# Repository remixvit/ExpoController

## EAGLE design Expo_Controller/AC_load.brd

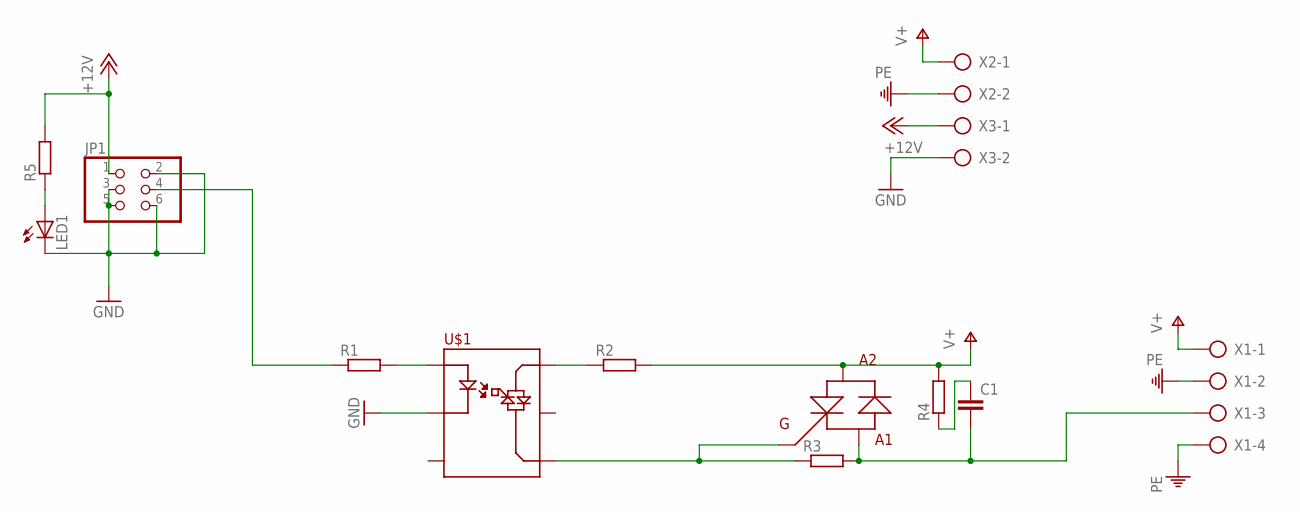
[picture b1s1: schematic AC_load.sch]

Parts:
C1: C-EU102-064X133; C102-064X133
JP1: PINHD-2X3; 2X03
LED1: LEDSML1206; SML1206
R1, R2, R3, R4, R5: R-EU_M1206; M1206
U$1: MOC3043; DIL06
U$2: BTB16; TO220NORM
X1: AK500/4
X2, X3: AK500/2

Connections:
+12V: JP1.1, R5.2, X3.1
GND: JP1.2, JP1.3, JP1.5, JP1.6, LED1.C, U$1.2 (LED_OUT), X3.2
unnamed: R1.2, U$1.1 (LED_IN)
unnamed: C1.2, R3.2, U$2.MT1 (A1), X1.3
unnamed: JP1.4, R1.1
unnamed: R3.1, U$1.4 (SIM2), U$2.GATE (G)
unnamed: R2.1, U$1.6 (SIM1)
unnamed: C1.1, R4.1
unnamed: LED1.A, R5.1
PE: X1.2, X1.4, X2.2
V+: R2.2, R4.2, U$2.MT2 (A2), X1.1, X2.1

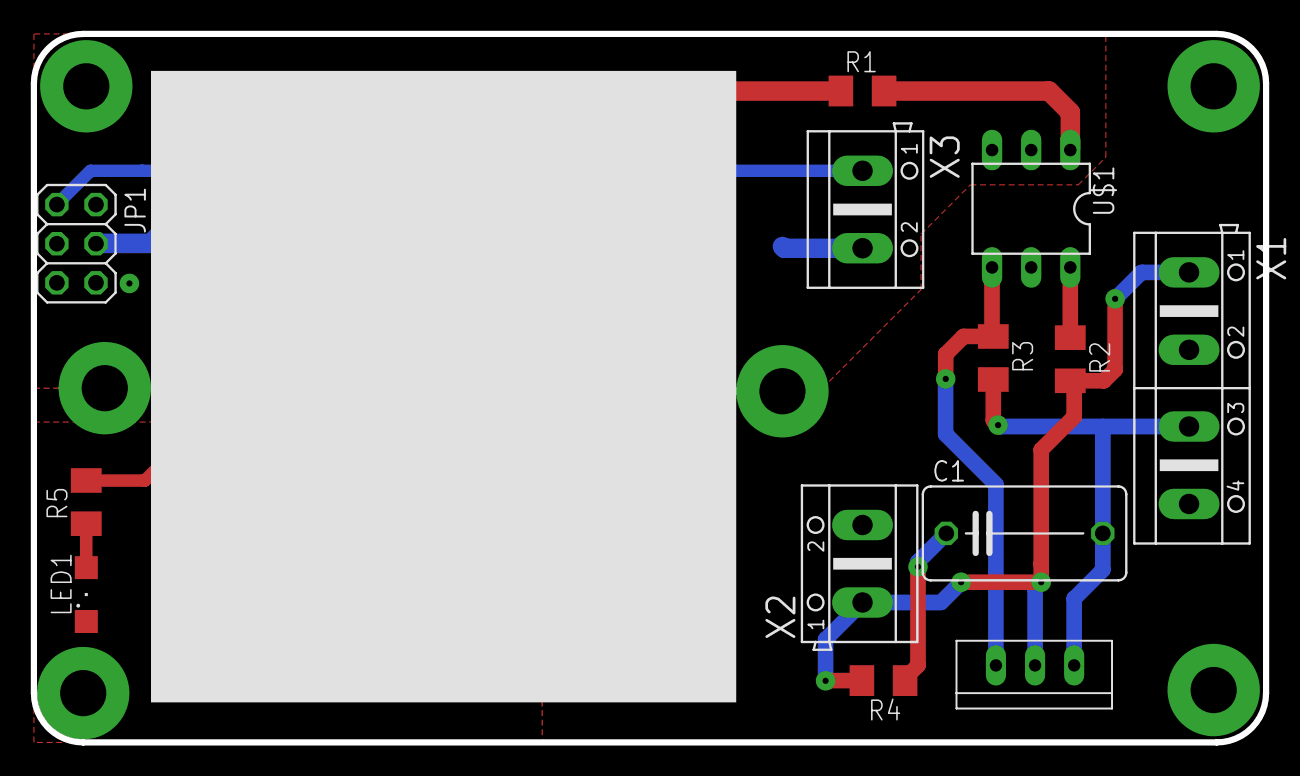
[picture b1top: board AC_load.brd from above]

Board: 2 copper layers, 80.0 x 46.0 mm, 13 parts (0 on the bottom side), 11 nets.

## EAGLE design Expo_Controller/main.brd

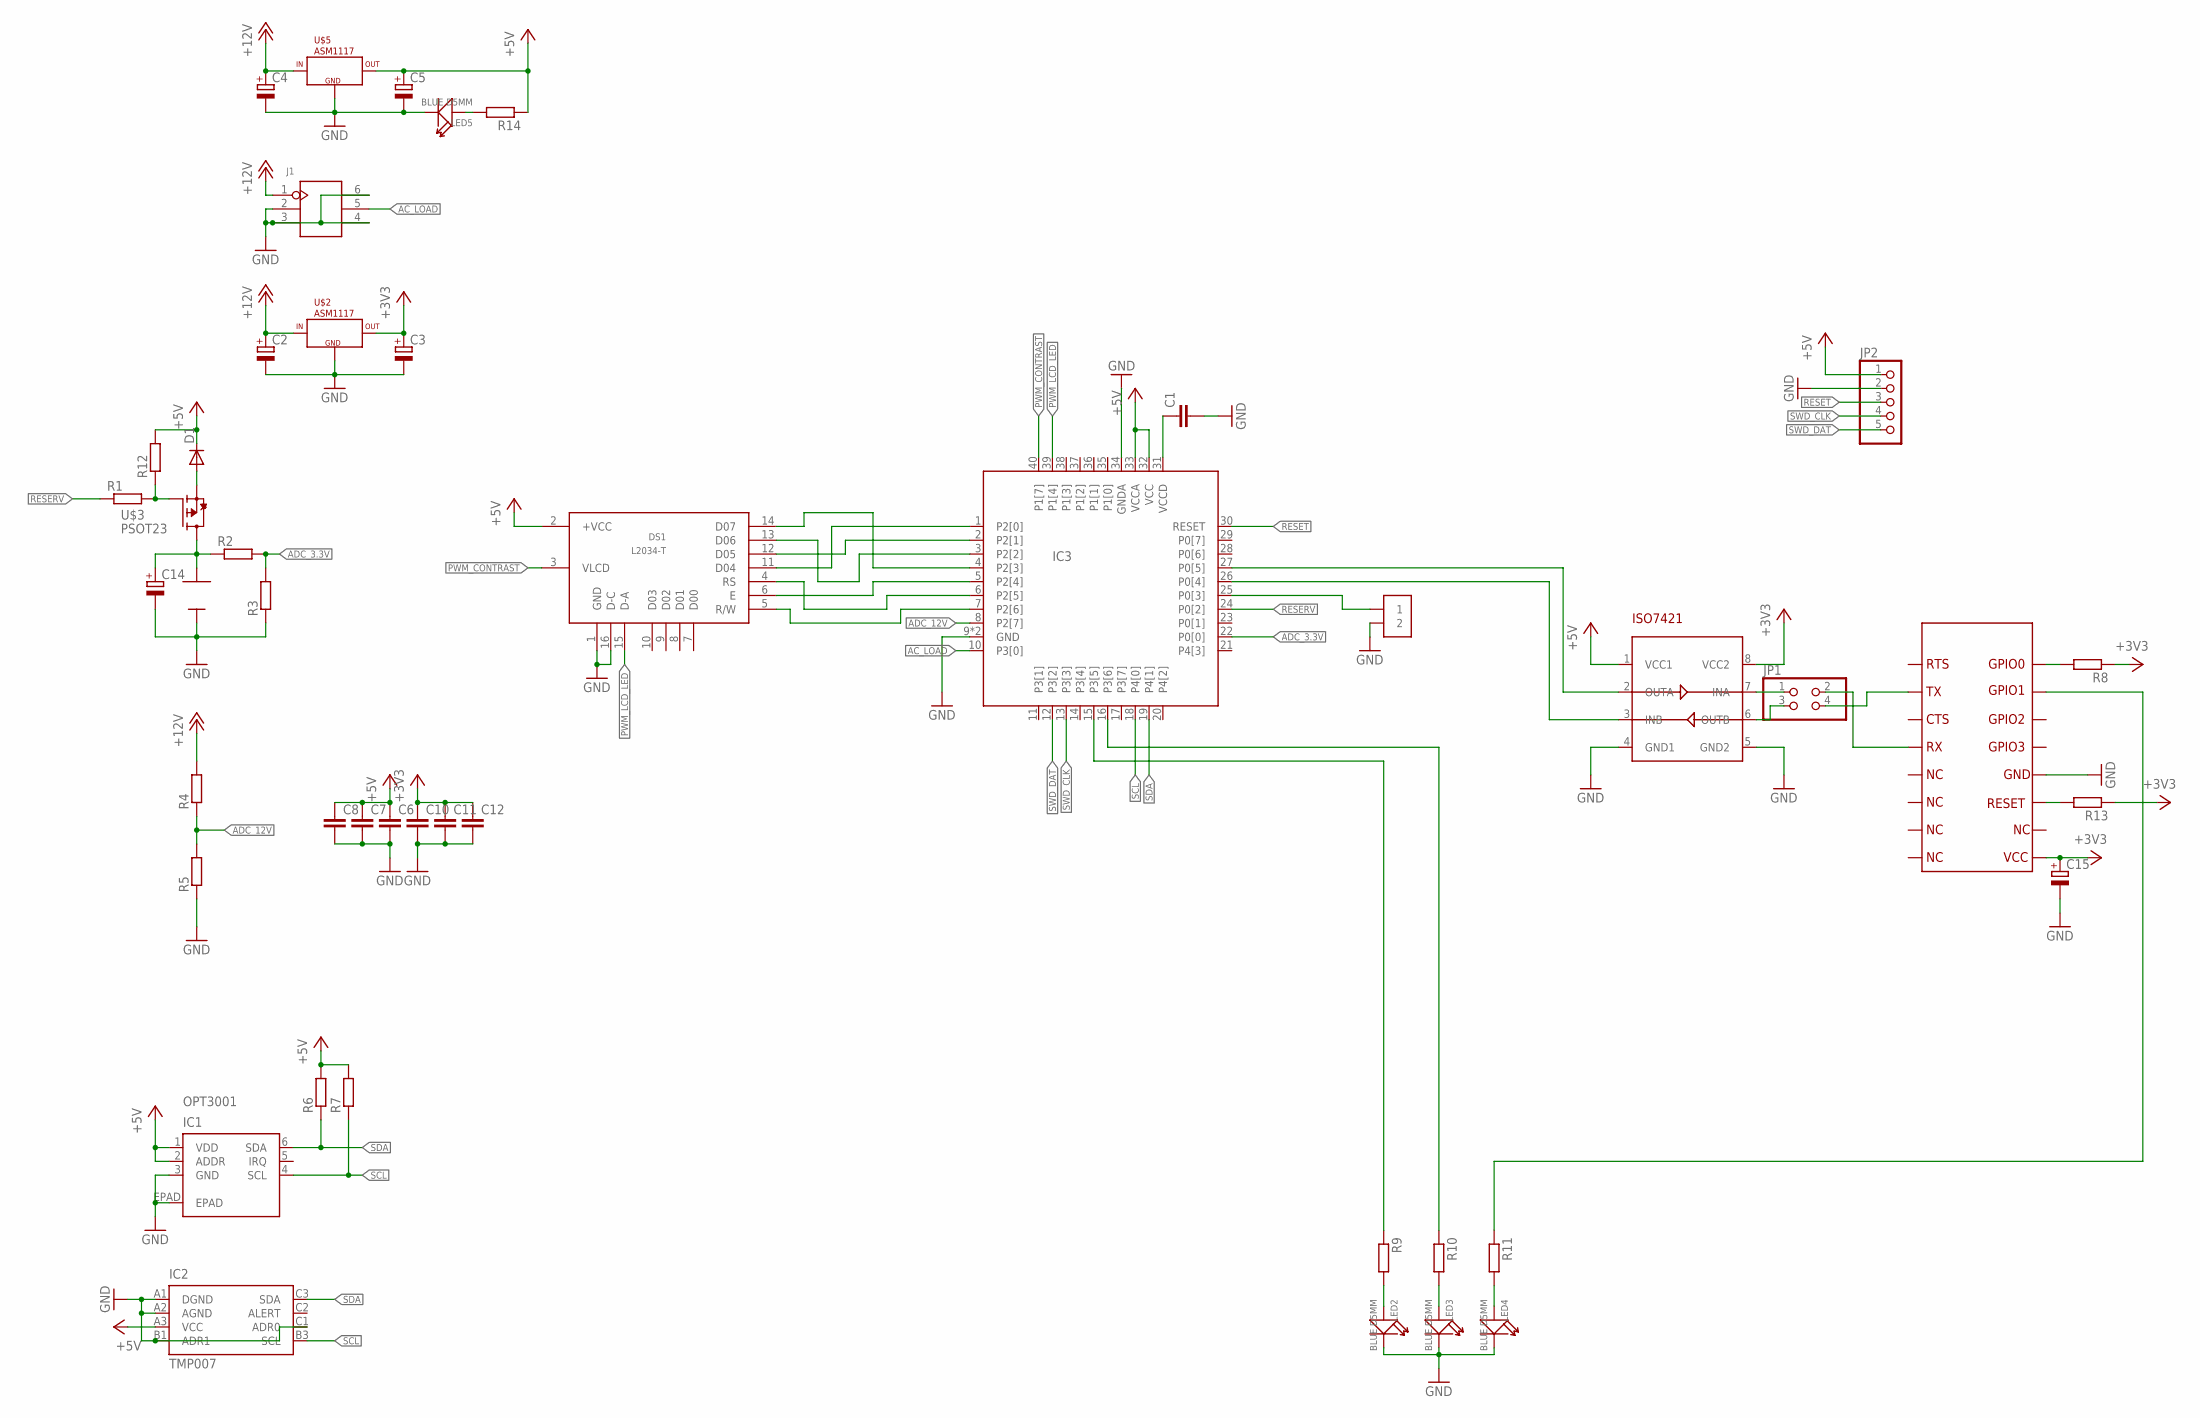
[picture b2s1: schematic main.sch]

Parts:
BAT1: CR2032_DIP
C1, C6, C7, C8, C10, C11, C12: C-EUC0805; C0805
C2, C3, C4, C5: CPOL-EU150CLZ-0810; 150CLZ-0810
C14: CPOL-EUSMCD; SMC_D
C15: CPOL-EUSMCA; SMC_A
D1: DIODE-DO-214AC; DO-214AC
DS1: L2034-T
IC1: OPT3001; USON6
IC2: TMP007; XBGA8
IC3: CY8C4245-LQI-LONG; QFN40-LONG
J1: DIP-BLUE-MALE-HEADER-VERT(2X3P-2.54); H2X3-2.54
JP1: PINHD-2X2; 2X02
JP2: PINHD-1X5; 1X05
LED2, LED3, LED4, LED5: BLUE D5MM; LED2-2.54-D5.0MM
R1, R2, R3, R4, R5, R6, R7, R8, R9, R10, R11, R12, R13, R14: R-EU_M0805; M0805
U$1: HM-11
U$2, U$5: ASM1117; SOT223
U$3: PSOT23; SOT23
U$6: ISO7421; SO8
U$7: 1X2

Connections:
+3V3: C3.+, C10.1, C11.1, C12.1, C15.+, R8.1, R13.1, U$1.9, U$2.2 (OUT), U$2.4 (OUT), U$6.8 (VCC2)
+5V: C5.+, C6.1, C7.1, C8.1, D1.C, DS1.2 (+VCC), IC1.1 (VDD), IC1.2 (ADDR), IC2.A3 (VCC), IC3.32 (VCC), IC3.33 (VCCA), JP2.1, R6.2, R7.2, R12.2, R14.1, U$5.2 (OUT), U$5.4 (OUT), U$6.1 (VCC1)
+12V: C2.+, C4.+, J1.1, R4.2, U$2.3 (IN), U$5.3 (IN)
AC_LOAD: IC3.10 (P3[0]), J1.5
ADC_3.3V: IC3.22 (P0[0]), R2.2, R3.2
ADC_12V: IC3.8 (P2[7]), R4.1, R5.2
GND: BAT1.-, C1.2, C2.-, C3.-, C4.-, C5.-, C6.2, C7.2, C8.2, C10.2, C11.2, C12.2, C14.-, C15.-, DS1.1 (GND), DS1.16 (D-C), IC1.3 (GND), IC1.EPAD, IC2.A1 (DGND), IC2.A2 (AGND), IC2.B1 (ADR1), IC2.C1 (ADR0), IC3.9 (GND), IC3.34 (GNDA), IC3.41 (GND), J1.2, J1.3, J1.4, J1.6, JP2.2, LED2.-, LED3.-, LED4.-, LED5.-, R3.1, R5.1, U$1.12, U$2.1 (GND), U$5.1 (GND), U$6.4 (GND1), U$6.5 (GND2), U$7.2
unnamed: IC3.25 (P0[3]), U$7.1
unnamed: C1.1, IC3.31 (VCCD)
unnamed: LED5.+, R14.2
unnamed: JP1.1, U$6.7 (INA)
unnamed: DS1.11 (D04), IC3.1 (P2[0])
unnamed: DS1.12 (D05), IC3.2 (P2[1])
unnamed: DS1.13 (D06), IC3.3 (P2[2])
unnamed: DS1.14 (D07), IC3.4 (P2[3])
unnamed: DS1.6 (E), IC3.5 (P2[4])
unnamed: DS1.4 (RS), IC3.6 (P2[5])
unnamed: DS1.5 (R/W), IC3.7 (P2[6])
unnamed: JP1.3, U$6.6 (OUTB)
unnamed: JP1.4, U$1.2
unnamed: R13.2, U$1.11
unnamed: JP1.2, U$1.4
unnamed: BAT1.+, C14.+, R2.1, U$3.S
unnamed: R1.2, R12.1, U$3.G
unnamed: R8.2, U$1.16
unnamed: LED2.+, R9.2
unnamed: LED3.+, R10.2
unnamed: LED4.+, R11.2
unnamed: R11.1, U$1.15
unnamed: IC3.16 (P3[6]), R10.1
unnamed: IC3.15 (P3[5]), R9.1
unnamed: IC3.27 (P0[5]), U$6.2 (OUTA)
unnamed: IC3.26 (P0[4]), U$6.3 (INB)
unnamed: D1.A, U$3.D
PWM_CONTRAST: DS1.3 (VLCD), IC3.40 (P1[7])
PWM_LCD_LED: DS1.15 (D-A), IC3.39 (P1[4])
RESERV: IC3.24 (P0[2]), R1.1
RESET: IC3.30 (RESET), JP2.3
SCL: IC1.4 (SCL), IC2.B3 (SCL), IC3.18 (P4[0]), R7.1
SDA: IC1.6 (SDA), IC2.C3 (SDA), IC3.19 (P4[1]), R6.1
SWD_CLK: IC3.13 (P3[3]), JP2.4
SWD_DAT: IC3.12 (P3[2]), JP2.5

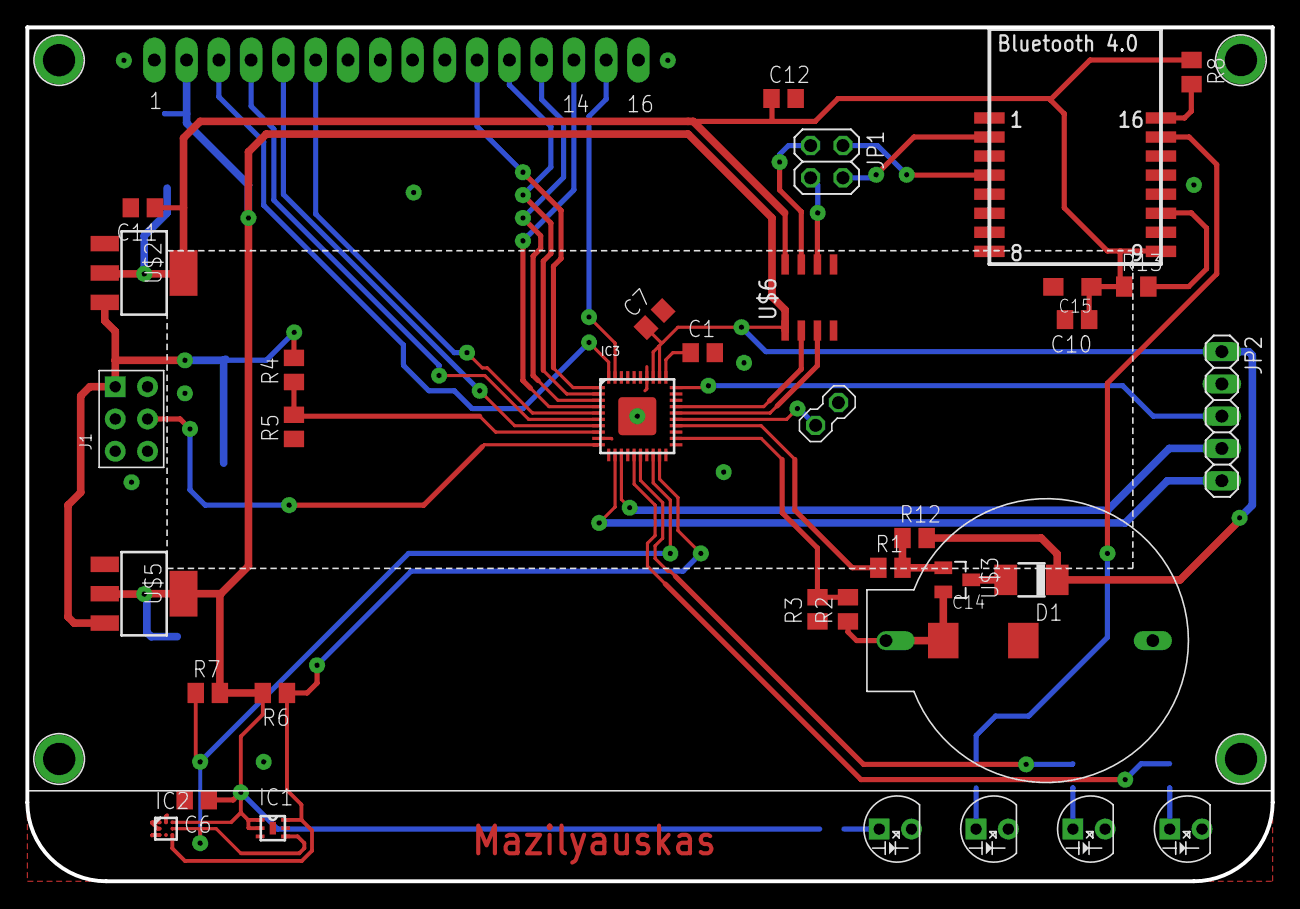
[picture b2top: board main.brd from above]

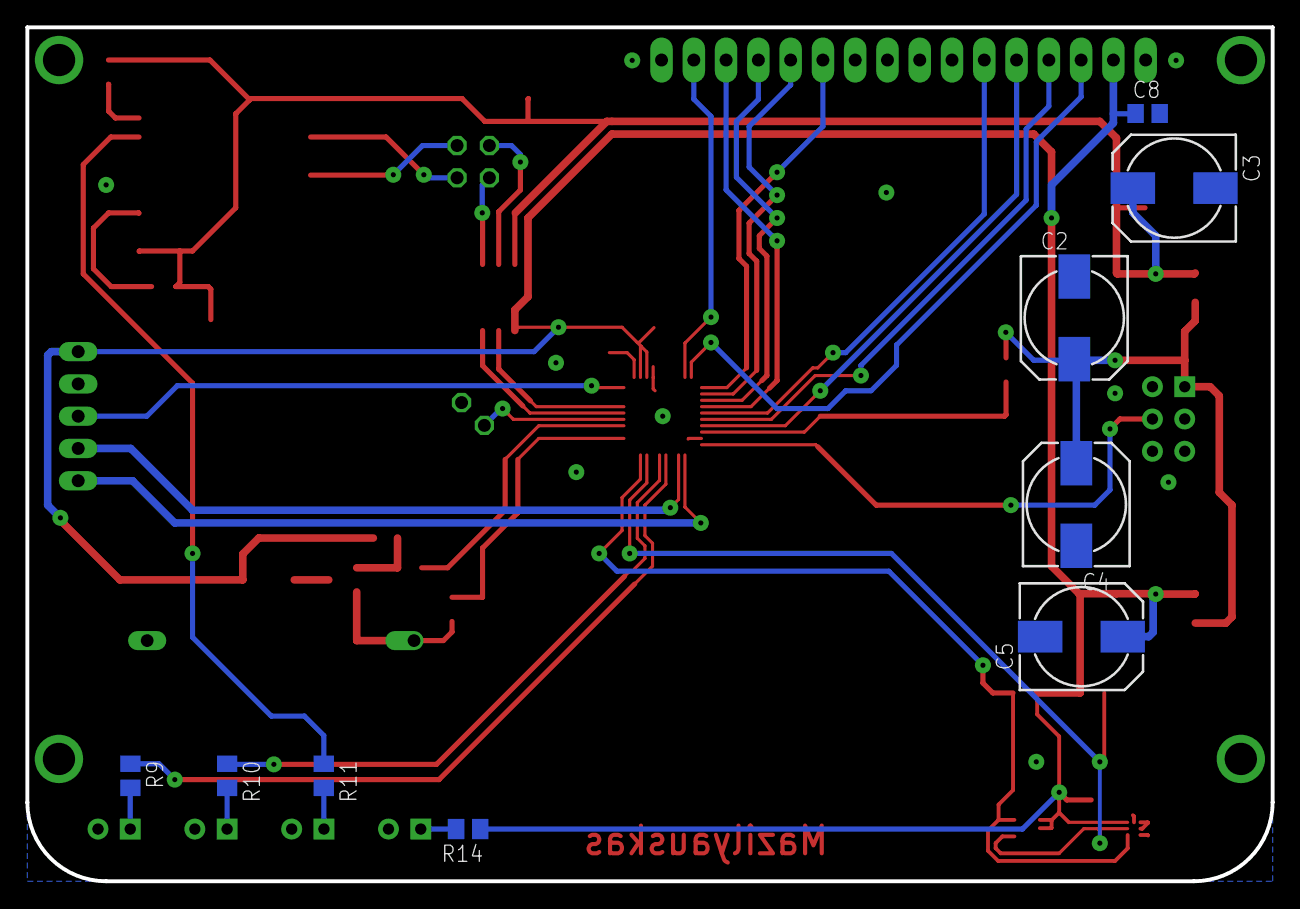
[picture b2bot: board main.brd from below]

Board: 2 copper layers, 98.0 x 67.2 mm, 46 parts (9 on the bottom side), 42 nets.

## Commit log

2015-11-22 Add To Git
2015-11-22 Add EagleCad Project
2015-11-23 Закончил разводку высоковольтного модуля
2015-11-23 Добавил функцию "Защитник Экрана" в библиотеку WS0010.h Добавил функцию вывода на экран таймера в одной строчке с часами. Добавил функцию расчета таймера исходя из реального времени и установленного 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
2015-11-24 Rebild
2015-11-24 Bug Fix
2015-12-01 Доработка Screensaer
2015-12-06 BugFix
